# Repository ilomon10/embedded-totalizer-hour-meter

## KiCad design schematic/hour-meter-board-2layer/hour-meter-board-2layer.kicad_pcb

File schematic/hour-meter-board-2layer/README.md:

# Hour Meter main board, 2-layer variant (rev B)

This is the [rev-B main board](../hour-meter-board/README.md) routed on **2 copper layers** instead of 4, for a cheaper PCB. The circuit, parts, BOM and placement are the same; only the copper layers and the routing differ. It takes the same plug-on [PSU-B](../hour-meter-psu-b/README.md).

The folder is a copy of `../hour-meter-board`, made the way KiCad's *File → Save As* makes one, so the 4-layer design is unchanged. The build, routing and finishing scripts are the main board's: `tools-pcb.py` here runs them on this folder's files with 2 layers.

| | |
|---|---|
| Schematic | `hour-meter-board-2layer.kicad_sch` + the 8 module sheets: a copy of the main board's, with the same netlist. For the circuit, connectors, jumpers and pin map, see the [main board README](../hour-meter-board/README.md) |
| PCB | `hour-meter-board-2layer.kicad_pcb`: 100 × 90 mm, 2 layers. F.Cu and B.Cu both carry tracks and a GND pour |
| Script | `tools-pcb.py` with `check`, `place`, `route [tries]`, `finish [passes]` or `production` |
| Order files | `production/`: Gerber zip, `BOM-hour-meter-board-2layer.csv`, `CPL-hour-meter-board-2layer.csv` (JLCPCB columns). The BOM and CPL are byte-identical to the 4-layer board's, so assembly is the same; only the bare PCB differs |

**Checks at this revision (2026-10-21):**
- **ERC:** same schematic as the main board: 0 errors, 2 intended warnings.
- **DRC:** 0 errors, 0 unconnected items, 0 schematic-parity issues. The 22 warnings are the same silkscreen ones as on the 4-layer board.
- **Routing:** with the IMU keep-outs in place, Freerouting's first try connected everything, so `finish` had nothing left to do.
- **Stock:** all parts are in JLCPCB stock for 10 boards.

## What changes with 2 layers

| | 4 layers (`hour-meter-board`) | 2 layers (this board) |
|---|---|---|
| GND | Solid In1.Cu plane; GND pads drop to it through vias | Routed as tracks, plus a GND pour on F.Cu and on B.Cu |
| +3V3 | Pour on In2.Cu | Routed as tracks (Plane netclass, 0.3 mm) |
| Signal layers | F.Cu, In2.Cu, B.Cu | F.Cu, B.Cu |
| Under the IMU (U601, U602) | In1.Cu GND plane shields the chips from the tracks below | Keep-outs on both layers: no tracks or vias, GND pour only (see below) |
| Silkscreen | `HOUR METER rev B` | `HOUR METER rev B`, plus `2-LAYER` to its left |

Unchanged: the outline, placement, parts, netclasses, via sizes (0.5/0.25 mm; 0.8/0.4 mm on power and vehicle nets), the copper keep-out under the antenna, and no pour on the vehicle side.

**IMU keep-outs.** The MPU-6500 datasheet prohibits routing under the package. It also asks for no active signals on unshielded layers directly below the gyro, because its drive frequencies (24–30 kHz) can couple in. With only 2 layers nothing shields B.Cu, so `tools-pcb.py place` adds rule areas under U601 and U602 (the LIS3MDL magnetometer gets the same treatment):
- **F.Cu:** the space inside the pad ring.
- **B.Cu:** the package plus 0.5 mm.

They keep tracks and vias out, but let the GND pours in. Keep them if you re-route by hand; KiCad's DRC flags anything that enters them.

## Before you order

The main board's [Before you order](../hour-meter-board/README.md#before-you-order) list applies here too. In addition:

1. **GND return paths.** Without a plane, tracks cut the GND pours into pieces that are joined by vias and the other layer's pour. DRC confirms GND is fully connected, but the paths can be long.
   - **Main split:** on B.Cu, a bundle of tracks running down from the ESP32 module to the ports (x ≈ 170–178 mm) divides the pour.
   - **What to do:** look at both pours in KiCad and add stitching vias along that bundle and wherever a piece hangs on a narrow neck, mainly around the ESP32, the USB parts (J201, U203, U202) and the IMU.
2. **USB D+/D−.** On a 1.6 mm 2-layer board, a 90 Ω pair would need traces about 1 mm wide. Keep the pair short, side by side and over unbroken GND on the other layer instead; at 12 Mbit/s that is enough.
3. **AMS1117 heat.** U204's tab has no +3V3 plane to spread heat into. If the ESP32 transmits a lot, give the tab more +3V3 copper.
4. **JLCPCB order:** 2 layers, 1.6 mm.
   - **Smallest holes:** the 0.25 mm routed vias (0.5 mm pad) and the ESP32's 0.2 mm thermal-pad vias (0.6 mm pad).
   - **Via price:** JLCPCB's [capabilities page](https://jlcpcb.com/capabilities/pcb-capabilities) (checked 2026-10-21) allows 0.15 mm via holes on 2-layer boards. It charges extra for a 0.2–0.25 mm hole only when the via is under 0.45 mm across, so these vias should be standard price. Check the price after you choose the via option on the order form.

## Re-generating the board

```bash
python3 tools-pcb.py place        # placement: PLACEMENT in ../hour-meter-board/tools-build-pcb.py
python3 tools-pcb.py route 4      # Freerouting x4, keep the best -> GND pours
python3 tools-pcb.py finish 3     # close what Freerouting left open (exit 1 if anything is still open)
kicad-cli pcb drc --severity-all --schematic-parity hour-meter-board-2layer.kicad_pcb
python3 tools-pcb.py production   # production/: Gerber zip, BOM, CPL
```

## Compact variant

[`../hour-meter-board-compact`](../hour-meter-board-compact/README.md) is a copy of this board on 80 × 70 mm. It also has milled isolation slots and the fault fixes from [`../fault-analysis`](../fault-analysis/README.md): a fault-protected RS485 transceiver and fused 5 V header pins.

## Keeping the two boards in step

- **Schematic:** this one is a copy, so a circuit change has to go into both. To check they still match, export each netlist with `kicad-cli sch export netlist` and diff them.
- **Placement:** a change to `PLACEMENT` in `../hour-meter-board/tools-build-pcb.py` moves parts on both boards the next time each one is placed.

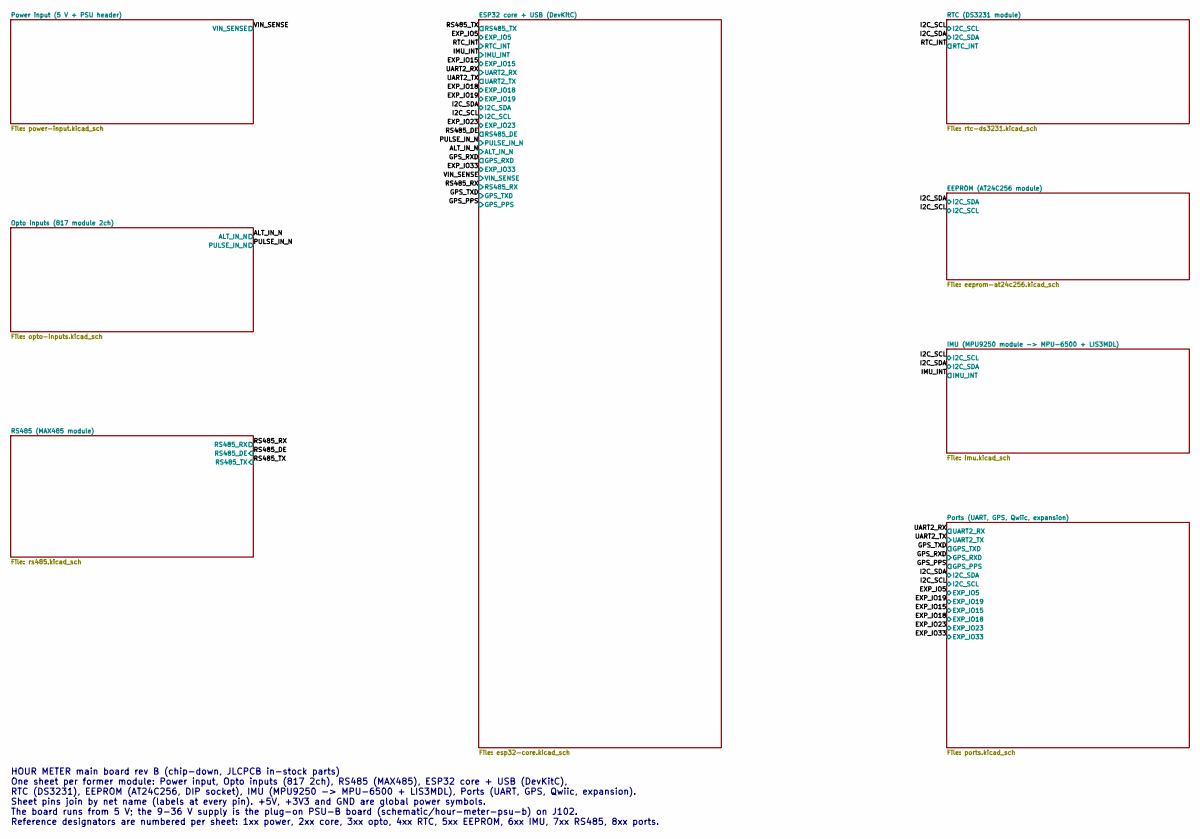
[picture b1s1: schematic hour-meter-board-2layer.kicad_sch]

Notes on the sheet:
HOUR METER main board rev B (chip-down, JLCPCB in-stock parts) One sheet per former module: Power input, Opto inputs (817 2ch), RS485 (MAX485), ESP32 core + USB (DevKitC), RTC (DS3231), EEPROM (AT24C256, DIP socket), IMU (MPU9250 -> MPU-6500 + LIS3MDL), Ports (UART, GPS, Qwiic, expansion). Sheet pi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

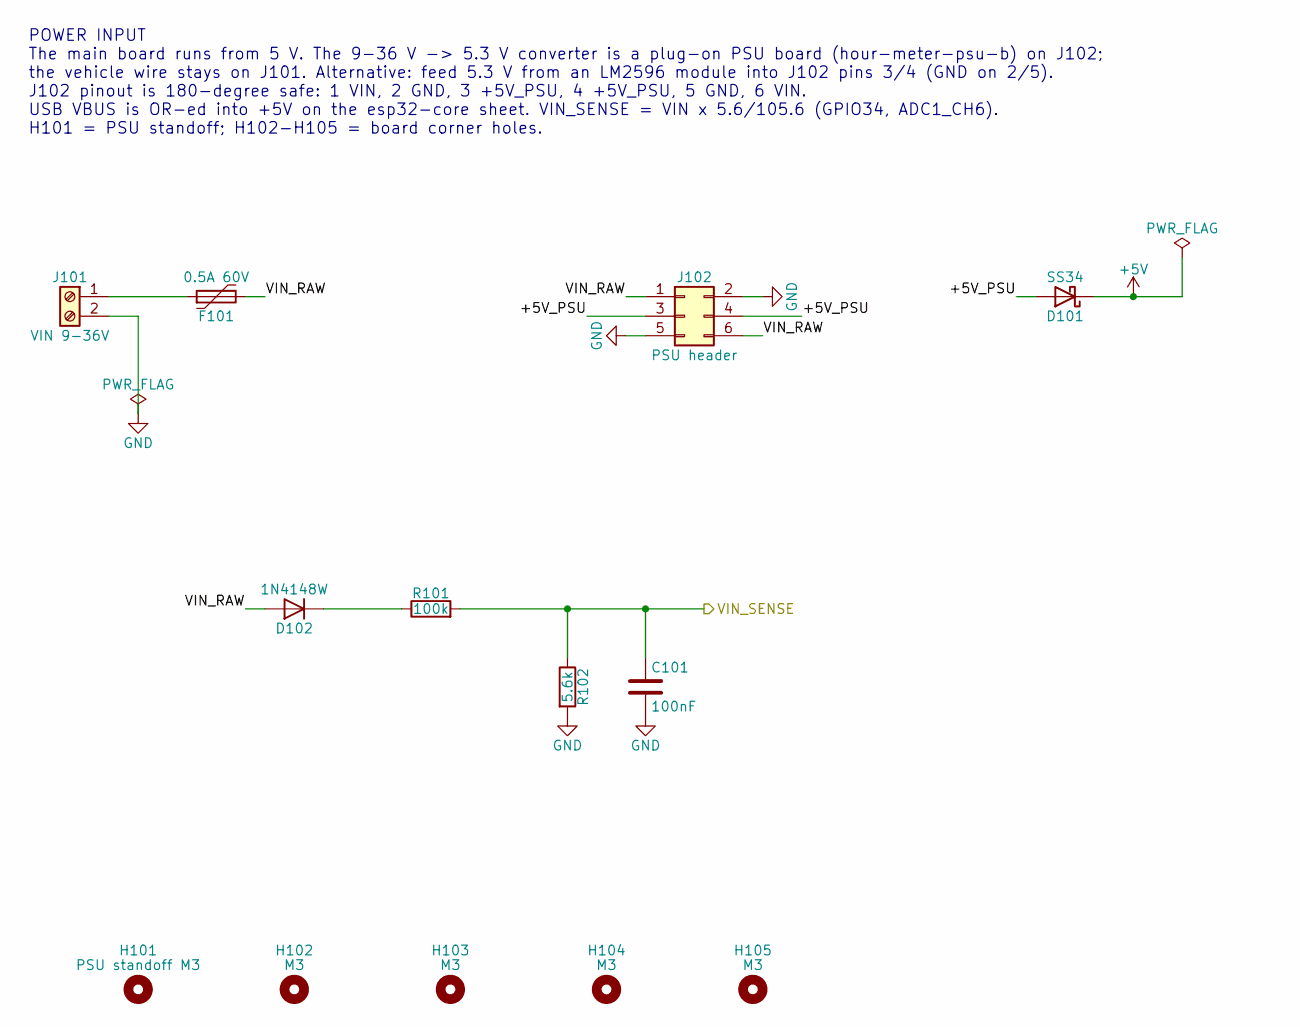
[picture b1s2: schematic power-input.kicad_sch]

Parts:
C101: 100nF; C_0603_1608Metric; MPN CC0603KRX7R9BB104; LCSC C14663
D101: SS34; D_SMA; MPN SS34; LCSC C8678
D102: 1N4148W; D_SOD-123; MPN 1N4148W; LCSC C81598
F101: 0.5A 60V; Fuse_1812_4532Metric; MPN 1812L050/60GR; LCSC C19078719
H101: PSU standoff M3; MountingHole_3.2mm_M3
H102, H103, H104, H105: M3; MountingHole_3.2mm_M3
J101: VIN 9-36V; TerminalBlock_Phoenix_MKDS-1,5-2-5.08_1x02_P5.08mm_Horizont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; MPN KF128-5.08-2P-AA; LCSC C474952
J102: PSU header; PinSocket_2x03_P2.54mm_Vertical; MPN A2541HWV-2x3P; LCSC C239343
R101: 100k; R_1206_3216Metric; MPN 1206W4F1003T5E; LCSC C17900
R102: 5.6k; R_0603_1608Metric; MPN 0603WAF5601T5E; LCSC C23189

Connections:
+5V: D101.1 (K); also elsewhere on the board
/Power input (5 V + PSU header)/+5V_PSU: D101.2 (A), J102.3, J102.4
/Power input (5 V + PSU header)/VIN_RAW: D102.2 (A), F101.2, J102.1, J102.6
/VIN_SENSE: C101.1, R101.2, R102.1; also elsewhere on the board
GND: C101.2, J101.2, J102.2, J102.5, R102.2; also elsewhere on the board
unnamed: D102.1 (K), R101.1
unnamed: F101.1, J101.1

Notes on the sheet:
POWER INPUT The main board runs from 5 V. The 9-36 V -> 5.3 V converter is a plug-on PSU board (hour-meter-psu-b) on J102; the vehicle wire stays on J101. Alternative: feed 5.3 V from an LM2596 module into J102 pins 3/4 (GND on 2/5). J102 pinout is 180-degree safe: 1 VIN, 2 GND, 3 +5V_PSU, 4 +5V_PS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

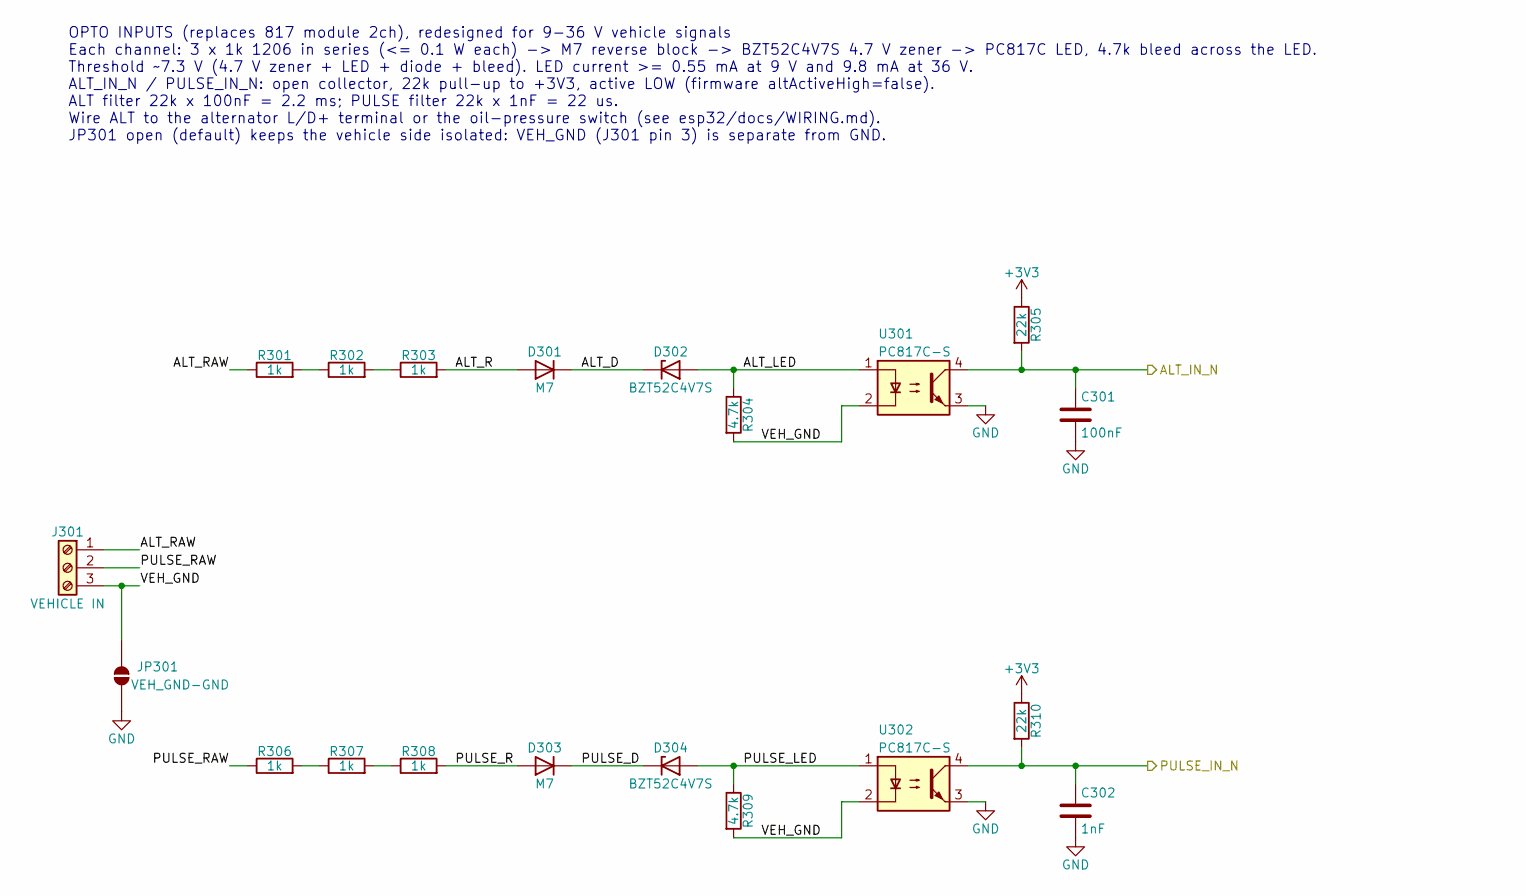
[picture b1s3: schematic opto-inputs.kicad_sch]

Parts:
C301: 100nF; C_0603_1608Metric; MPN CC0603KRX7R9BB104; LCSC C14663
C302: 1nF; C_0603_1608Metric; MPN CL10B102KB8NNNC; LCSC C1588
D301, D303: M7; D_SMA; MPN M7; LCSC C82443
D302, D304: BZT52C4V7S; D_SOD-323; MPN BZT52C4V7S; LCSC C22611
J301: VEHICLE IN; TerminalBlock_Phoenix_MKDS-1,5-3-5.08_1x03_P5.08mm_Horizont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; MPN KF128-5.08-3P-AA; LCSC C474953
JP301: VEH_GND-GND; SolderJumper-2_P1.3mm_Open_RoundedPad1.0x1.5mm
R301, R302, R303, R306, R307, R308: 1k; R_1206_3216Metric; MPN 1206W4F1001T5E; LCSC C4410
R304, R309: 4.7k; R_0603_1608Metric; MPN 0603WAF4701T5E; LCSC C23162
R305, R310: 22k; R_0603_1608Metric; MPN 0603WAF2202T5E; LCSC C31850
U301, U302: PC817C-S; SMDIP-4_W9.53mm; MPN PC817C-S; LCSC C3008369

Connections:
+3V3: R305.1, R310.1; also elsewhere on the board
/ALT_IN_N: C301.1, R305.2, U301.4; also elsewhere on the board
/Opto inputs (817 module 2ch)/ALT_D: D301.1 (K), D302.1 (K)
/Opto inputs (817 module 2ch)/ALT_LED: D302.2 (A), R304.1, U301.1
/Opto inputs (817 module 2ch)/ALT_R: D301.2 (A), R303.2
/Opto inputs (817 module 2ch)/ALT_RAW: J301.1, R301.1
/Opto inputs (817 module 2ch)/PULSE_D: D303.1 (K), D304.1 (K)
/Opto inputs (817 module 2ch)/PULSE_LED: D304.2 (A), R309.1, U302.1
/Opto inputs (817 module 2ch)/PULSE_R: D303.2 (A), R308.2
/Opto inputs (817 module 2ch)/PULSE_RAW: J301.2, R306.1
/Opto inputs (817 module 2ch)/VEH_GND: J301.3, JP301.1 (A), R304.2, R309.2, U301.2, U302.2
/PULSE_IN_N: C302.1, R310.2, U302.4; also elsewhere on the board
GND: C301.2, C302.2, JP301.2 (B), U301.3, U302.3; also elsewhere on the board
unnamed: R301.2, R302.1
unnamed: R302.2, R303.1
unnamed: R306.2, R307.1
unnamed: R307.2, R308.1

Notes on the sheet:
OPTO INPUTS (replaces 817 module 2ch), redesigned for 9-36 V vehicle signals Each channel: 3 x 1k 1206 in series (<= 0.1 W each) -> M7 reverse block -> BZT52C4V7S 4.7 V zener -> PC817C LED, 4.7k bleed across the LED. Threshold ~7.3 V (4.7 V zener + LED + diode + bleed). LED current >= 0.55 mA at 9 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

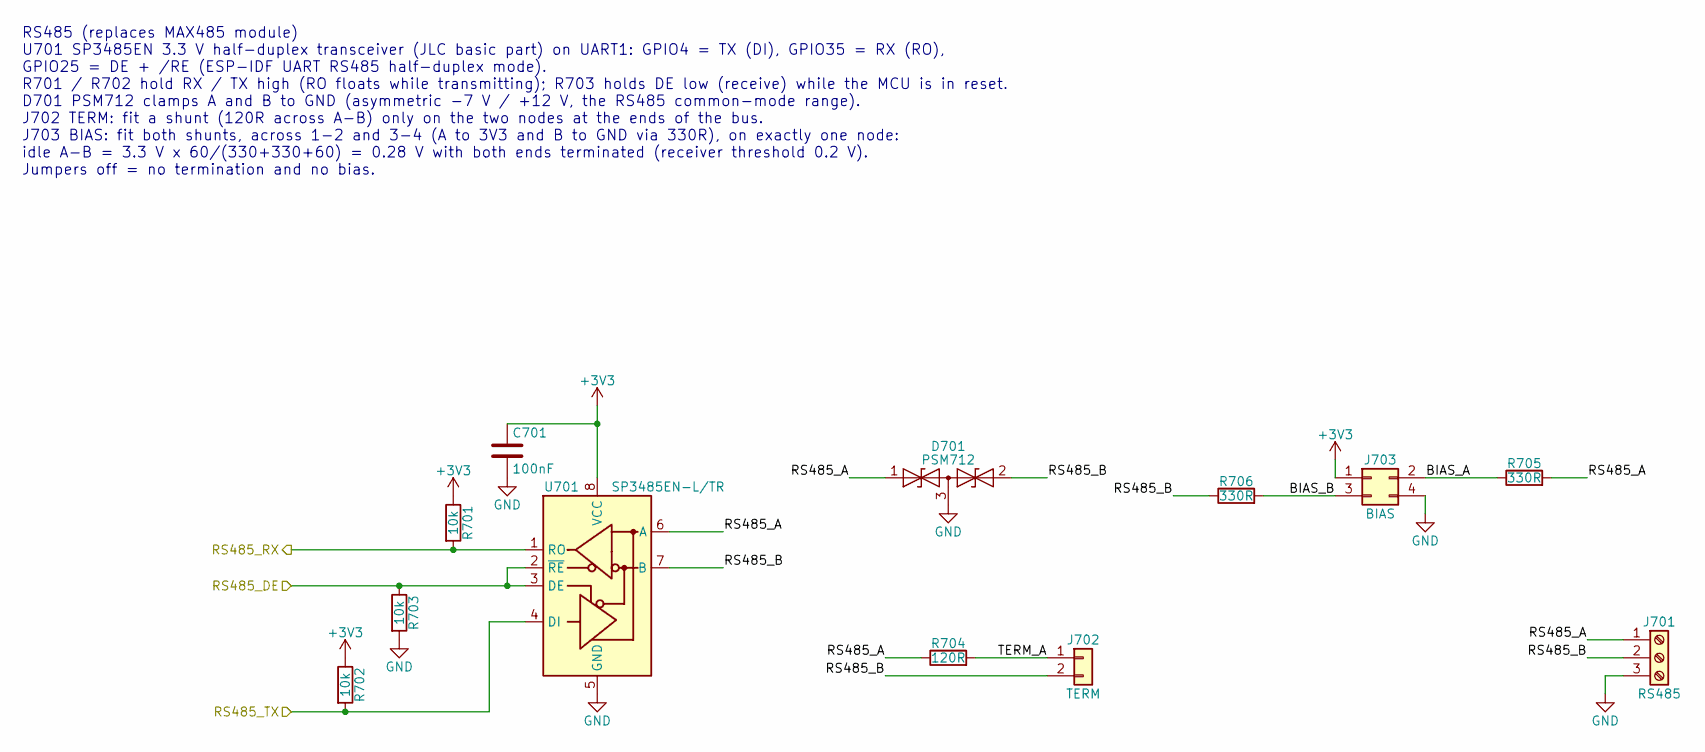
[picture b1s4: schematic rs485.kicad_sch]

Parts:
C701: 100nF; C_0603_1608Metric; MPN CC0603KRX7R9BB104; LCSC C14663
D701: PSM712; SOT-23; MPN PSM712-LF-T7; LCSC C32677
J701: RS485; TerminalBlock_Phoenix_MKDS-1,5-3-5.08_1x03_P5.08mm_Horizont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; MPN KF128-5.08-3P-AA; LCSC C474953
J702: TERM; PinHeader_1x02_P2.54mm_Vertical; MPN 254PZ-1x2P-V; LCSC C53055672
J703: BIAS; PinHeader_2x02_P2.54mm_Vertical; MPN 2.54-2*2PPin; LCSC C66690
R701, R702, R703: 10k; R_0603_1608Metric; MPN 0603WAF1002T5E; LCSC C25804
R704: 120R; R_0805_2012Metric; MPN 0805W8F1200T5E; LCSC C17437
R705, R706: 330R; R_0603_1608Metric; MPN 0603WAF3300T5E; LCSC C23138
U701: SP3485EN-L/TR; SOIC-8_3.9x4.9mm_P1.27mm; MPN SP3485EN-L/TR; LCSC C8963

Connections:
+3V3: C701.1, J703.1, R701.1, R702.1, U701.8 (VCC); also elsewhere on the board
/RS485 (MAX485 module)/BIAS_A: J703.2, R705.1
/RS485 (MAX485 module)/BIAS_B: J703.3, R706.2
/RS485 (MAX485 module)/RS485_A: D701.1 (A1), J701.1, R704.1, R705.2, U701.6 (A)
/RS485 (MAX485 module)/RS485_B: D701.2 (A2), J701.2, J702.2, R706.1, U701.7 (B)
/RS485 (MAX485 module)/TERM_A: J702.1, R704.2
/RS485_DE: R703.1, U701.2 (~RE), U701.3 (DE); also elsewhere on the board
/RS485_RX: R701.2, U701.1 (RO); also elsewhere on the board
/RS485_TX: R702.2, U701.4 (DI); also elsewhere on the board
GND: C701.2, D701.3 (common), J701.3, J703.4, R703.2, U701.5 (GND); also elsewhere on the board

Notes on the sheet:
RS485 (replaces MAX485 module) U701 SP3485EN 3.3 V half-duplex transceiver (JLC basic part) on UART1: GPIO4 = TX (DI), GPIO35 = RX (RO), GPIO25 = DE + /RE (ESP-IDF UART RS485 half-duplex mode). R701 / R702 hold RX / TX high (RO floats while transmitting); R703 holds DE low (receive) while the MCU i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

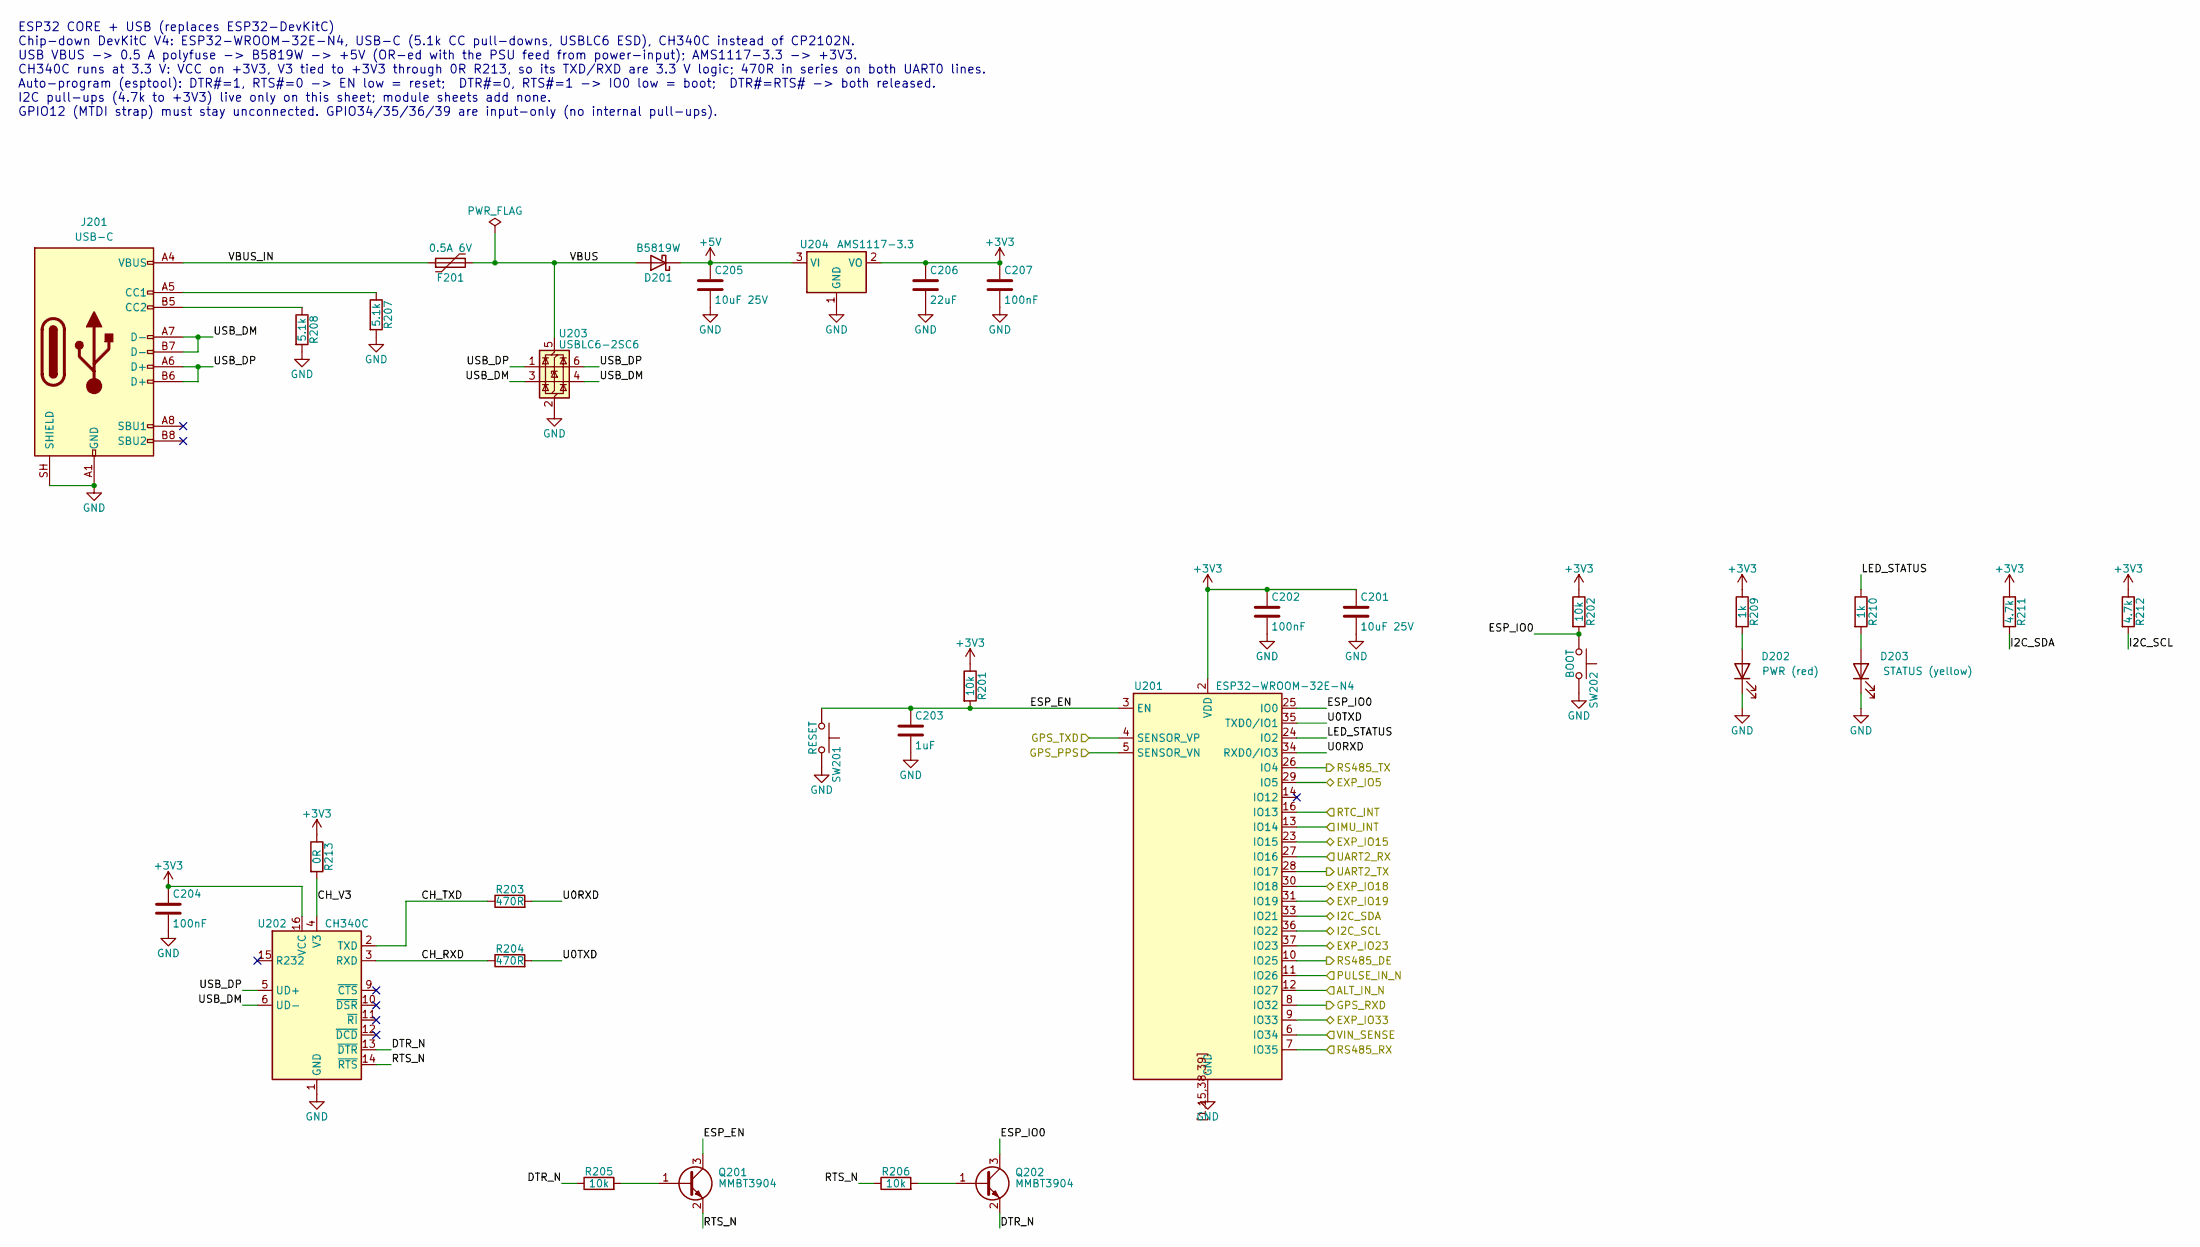
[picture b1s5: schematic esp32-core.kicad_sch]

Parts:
C201, C205: 10uF 25V; C_0805_2012Metric; MPN CL21A106KAYNNNE; LCSC C15850
C202, C204, C207: 100nF; C_0603_1608Metric; MPN CC0603KRX7R9BB104; LCSC C14663
C203: 1uF; C_0603_1608Metric; MPN CL10A105KB8NNNC; LCSC C15849
C206: 22uF; C_0805_2012Metric; MPN CL21A226MAQNNNE; LCSC C45783
D201: B5819W; D_SOD-123; MPN B5819W SL; LCSC C8598
D202: PWR (red); LED_0603_1608Metric; MPN KT-0603R; LCSC C2286
D203: STATUS (yellow); LED_0603_1608Metric; MPN KT-0603Y; LCSC C2287
F201: 0.5A 6V; Fuse_1206_3216Metric; MPN nSMD050; LCSC C69688
J201: USB-C; USB_C_Receptacle_HRO_TYPE-C-31-M-12; MPN TYPE-C-31-M-12; LCSC C165948
Q201, Q202: MMBT3904; SOT-23; MPN MMBT3904; LCSC C20526
R201, R202, R205, R206: 10k; R_0603_1608Metric; MPN 0603WAF1002T5E; LCSC C25804
R203, R204: 470R; R_0603_1608Metric; MPN 0603WAF4700T5E; LCSC C23179
R207, R208: 5.1k; R_0603_1608Metric; MPN 0603WAF5101T5E; LCSC C23186
R209, R210: 1k; R_0603_1608Metric; MPN 0603WAF1001T5E; LCSC C21190
R211, R212: 4.7k; R_0603_1608Metric; MPN 0603WAF4701T5E; LCSC C23162
R213: 0R; R_0603_1608Metric; MPN 0603WAF0000T5E; LCSC C21189
SW201: RESET; SW_Push_1P1T_XKB_TS-1187A; MPN TS-1187A-B-A-B; LCSC C318884
SW202: BOOT; SW_Push_1P1T_XKB_TS-1187A; MPN TS-1187A-B-A-B; LCSC C318884
U201: ESP32-WROOM-32E-N4; ESP32-WROOM-32E; MPN ESP32-WROOM-32E-N4; LCSC C701341
U202: CH340C; SOIC-16_3.9x9.9mm_P1.27mm; MPN CH340C; LCSC C84681
U203: USBLC6-2SC6; SOT-23-6; MPN USBLC6-2SC6; LCSC C7519
U204: AMS1117-3.3; SOT-223-3_TabPin2; MPN AMS1117-3.3; LCSC C6186

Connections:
+3V3: C201.1, C202.1, C204.1, C206.1, C207.1, R201.1, R202.1, R209.1, R211.1, R212.1, R213.1, U201.2 (VDD), U202.16 (VCC), U204.2 (VO); also elsewhere on the board
+5V: C205.1, D201.1 (K), U204.3 (VI); also elsewhere on the board
/ALT_IN_N: U201.12 (IO27); also elsewhere on the board
/ESP32 core + USB (DevKitC)/CH_RXD: R204.1, U202.3 (RXD)
/ESP32 core + USB (DevKitC)/CH_TXD: R203.1, U202.2 (TXD)
/ESP32 core + USB (DevKitC)/CH_V3: R213.2, U202.4 (V3)
/ESP32 core + USB (DevKitC)/DTR_N: Q202.2 (E), R205.1, U202.13 (~DTR)
/ESP32 core + USB (DevKitC)/ESP_EN: C203.1, Q201.3 (C), R201.2, SW201.1, U201.3 (EN)
/ESP32 core + USB (DevKitC)/ESP_IO0: Q202.3 (C), R202.2, SW202.1, U201.25 (IO0)
/ESP32 core + USB (DevKitC)/LED_STATUS: R210.1, U201.24 (IO2)
/ESP32 core + USB (DevKitC)/RTS_N: Q201.2 (E), R206.1, U202.14 (~RTS)
/ESP32 core + USB (DevKitC)/U0RXD: R203.2, U201.34 (RXD0/IO3)
/ESP32 core + USB (DevKitC)/U0TXD: R204.2, U201.35 (TXD0/IO1)
/ESP32 core + USB (DevKitC)/USB_DM: J201.A7 (D-), J201.B7 (D-), U202.6 (UD-), U203.3 (I/O2), U203.4 (I/O2)
/ESP32 core + USB (DevKitC)/USB_DP: J201.A6 (D+), J201.B6 (D+), U202.5 (UD+), U203.1 (I/O1), U203.6 (I/O1)
/ESP32 core + USB (DevKitC)/VBUS: D201.2 (A), F201.2, U203.5 (VBUS)
/ESP32 core + USB (DevKitC)/VBUS_IN: F201.1, J201.A4 (VBUS), J201.A9 (VBUS), J201.B4 (VBUS), J201.B9 (VBUS)
/EXP_IO5: U201.29 (IO5); also elsewhere on the board
/EXP_IO15: U201.23 (IO15); also elsewhere on the board
/EXP_IO18: U201.30 (IO18); also elsewhere on the board
/EXP_IO19: U201.31 (IO19); also elsewhere on the board
/EXP_IO23: U201.37 (IO23); also elsewhere on the board
/EXP_IO33: U201.9 (IO33); also elsewhere on the board
/GPS_PPS: U201.5 (SENSOR_VN); also elsewhere on the board
/GPS_RXD: U201.8 (IO32); also elsewhere on the board
/GPS_TXD: U201.4 (SENSOR_VP); also elsewhere on the board
/I2C_SCL: R212.2, U201.36 (IO22); also elsewhere on the board
/I2C_SDA: R211.2, U201.33 (IO21); also elsewhere on the board
/IMU_INT: U201.13 (IO14); also elsewhere on the board
/PULSE_IN_N: U201.11 (IO26); also elsewhere on the board
/RS485_DE: U201.10 (IO25); also elsewhere on the board
/RS485_RX: U201.7 (IO35); also elsewhere on the board
/RS485_TX: U201.26 (IO4); also elsewhere on the board
/RTC_INT: U201.16 (IO13); also elsewhere on the board
/UART2_RX: U201.27 (IO16); also elsewhere on the board
/UART2_TX: U201.28 (IO17); also elsewhere on the board
/VIN_SENSE: U201.6 (IO34); also elsewhere on the board
GND: C201.2, C202.2, C203.2, C204.2, C205.2, C206.2, C207.2, D202.1 (K), D203.1 (K), J201.A1 (GND), J201.A12 (GND), J201.B1 (GND), J201.B12 (GND), J201.SH (SHIELD), R207.2, R208.2, SW201.2, SW202.2, U201.1, U201.15, U201.38, U201.39, U201.[1,15,38,39] (GND), U202.1 (GND), U203.2 (GND), U204.1 (GND); also elsewhere on the board
unnamed: D202.2 (A), R209.2
unnamed: D203.2 (A), R210.2
unnamed: J201.A5 (CC1), R207.1
unnamed: J201.B5 (CC2), R208.1
unnamed: Q201.1 (B), R205.2
unnamed: Q202.1 (B), R206.2

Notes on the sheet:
ESP32 CORE + USB (replaces ESP32-DevKitC) Chip-down DevKitC V4: ESP32-WROOM-32E-N4, USB-C (5.1k CC pull-downs, USBLC6 ESD), CH340C instead of CP2102N. USB VBUS -> 0.5 A polyfuse -> B5819W -> +5V (OR-ed with the PSU feed from power-input); AMS1117-3.3 -> +3V3. CH340C runs at 3.3 V: VCC on +3V3, V3 t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

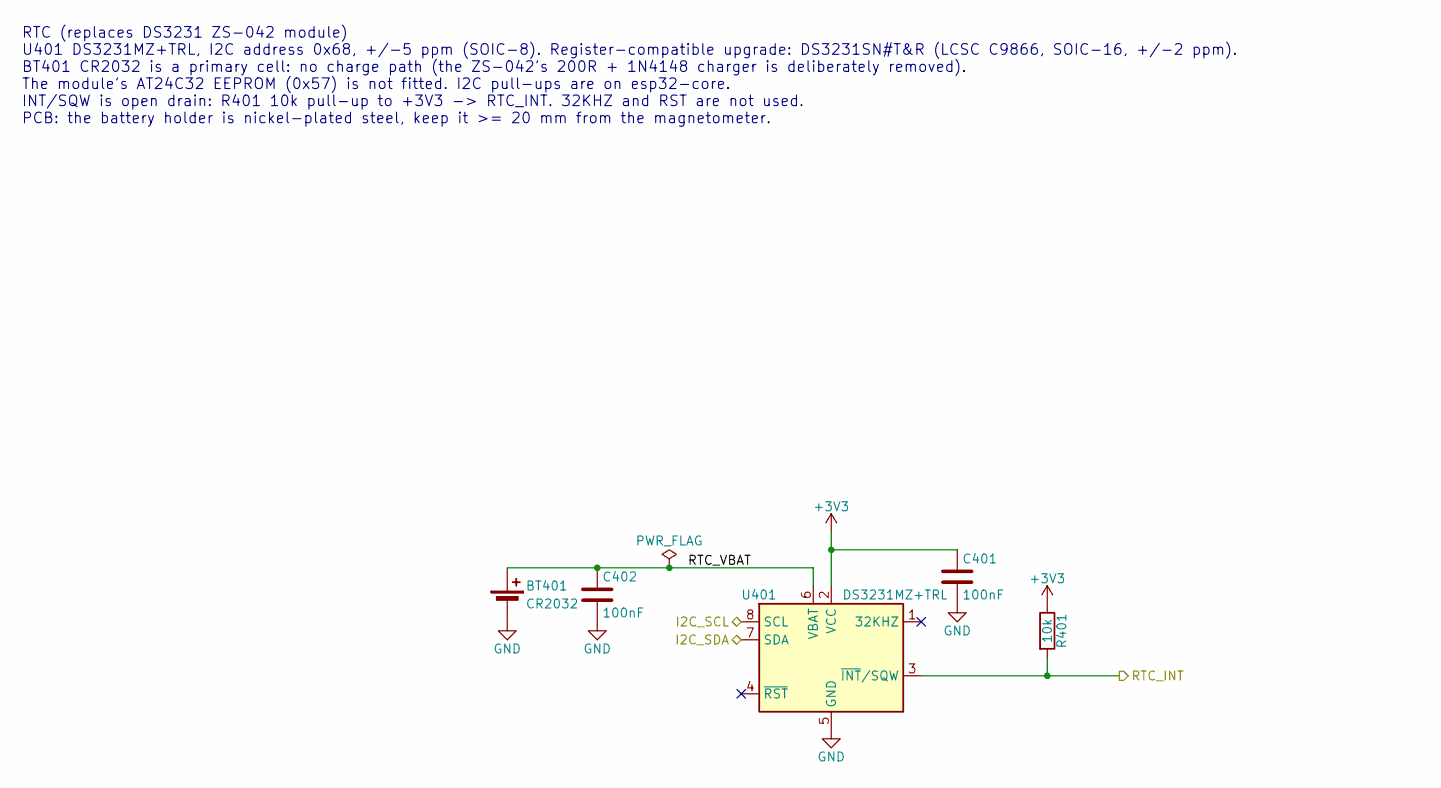
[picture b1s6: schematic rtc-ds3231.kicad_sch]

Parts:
BT401: CR2032; BatteryHolder_MYOUNG_BS-07-A1BJ001_CR2032; MPN BS-07-A1BJ001; LCSC C2979167
C401, C402: 100nF; C_0603_1608Metric; MPN CC0603KRX7R9BB104; LCSC C14663
R401: 10k; R_0603_1608Metric; MPN 0603WAF1002T5E; LCSC C25804
U401: DS3231MZ+TRL; SOIC-8_3.9x4.9mm_P1.27mm; MPN DS3231MZ+TRL; LCSC C107410

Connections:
+3V3: C401.1, R401.1, U401.2 (VCC); also elsewhere on the board
/I2C_SCL: U401.8 (SCL); also elsewhere on the board
/I2C_SDA: U401.7 (SDA); also elsewhere on the board
/RTC (DS3231 module)/RTC_VBAT: BT401.1 (+), C402.1, U401.6 (VBAT)
/RTC_INT: R401.2, U401.3 (~INT/SQW); also elsewhere on the board
GND: BT401.2 (-), C401.2, C402.2, U401.5 (GND); also elsewhere on the board

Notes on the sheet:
RTC (replaces DS3231 ZS-042 module) U401 DS3231MZ+TRL, I2C address 0x68, +/-5 ppm (SOIC-8). Register-compatible upgrade: DS3231SN#T&R (LCSC C9866, SOIC-16, +/-2 ppm). BT401 CR2032 is a primary cell: no charge path (the ZS-042's 200R + 1N4148 charger is deliberately removed). The module's AT24C32 EE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

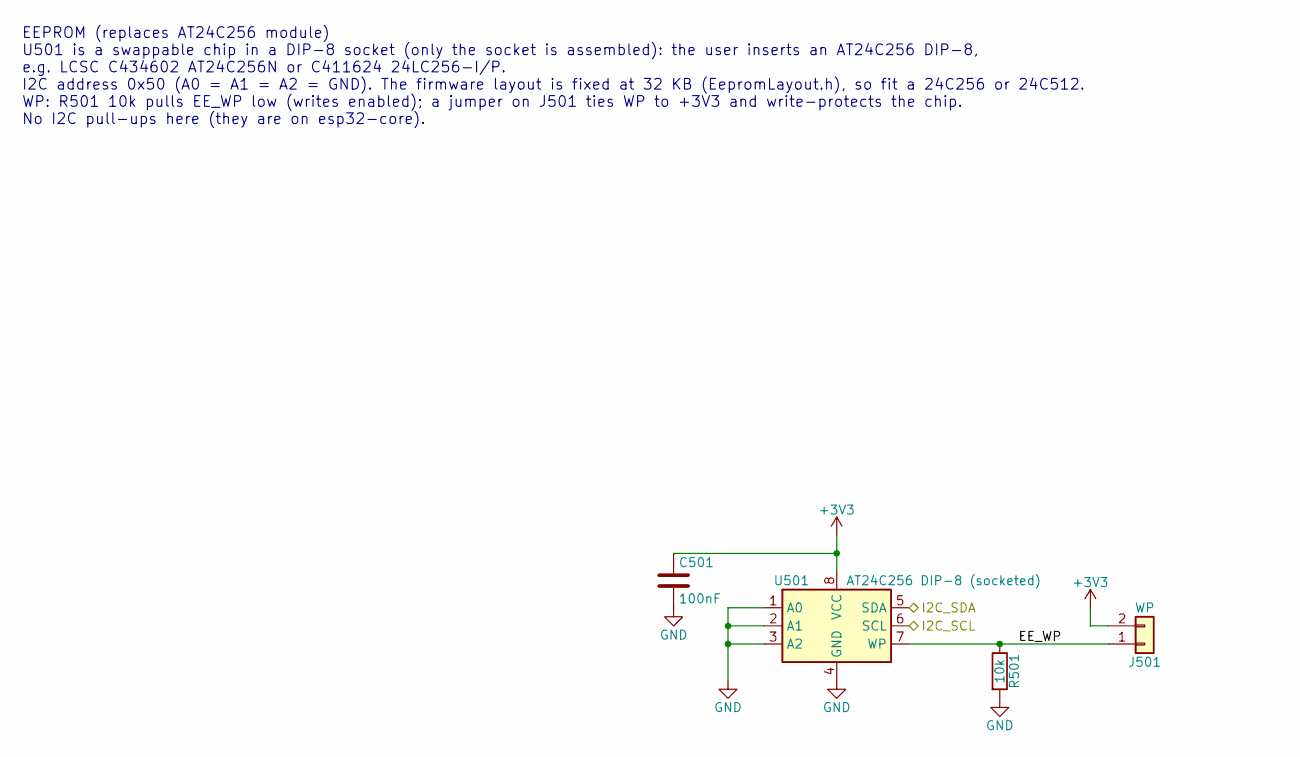
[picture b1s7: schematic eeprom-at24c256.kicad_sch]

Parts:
C501: 100nF; C_0603_1608Metric; MPN CC0603KRX7R9BB104; LCSC C14663
J501: WP; PinHeader_1x02_P2.54mm_Vertical; MPN 254PZ-1x2P-V; LCSC C53055672
R501: 10k; R_0603_1608Metric; MPN 0603WAF1002T5E; LCSC C25804
U501: AT24C256 DIP-8 (socketed); DIP-8_W7.62mm_Socket; MPN IC254V-12-08-0743; LCSC C2874007

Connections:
+3V3: C501.1, J501.2, U501.8 (VCC); also elsewhere on the board
/EEPROM (AT24C256 module)/EE_WP: J501.1, R501.1, U501.7 (WP)
/I2C_SCL: U501.6 (SCL); also elsewhere on the board
/I2C_SDA: U501.5 (SDA); also elsewhere on the board
GND: C501.2, R501.2, U501.1 (A0), U501.2 (A1), U501.3 (A2), U501.4 (GND); also elsewhere on the board

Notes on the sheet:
EEPROM (replaces AT24C256 module) U501 is a swappable chip in a DIP-8 socket (only the socket is assembled): the user inserts an AT24C256 DIP-8, e.g. LCSC C434602 AT24C256N or C411624 24LC256-I/P. I2C address 0x50 (A0 = A1 = A2 = GND). The firmware layout is fixed at 32 KB (EepromLayout.h), so fit 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

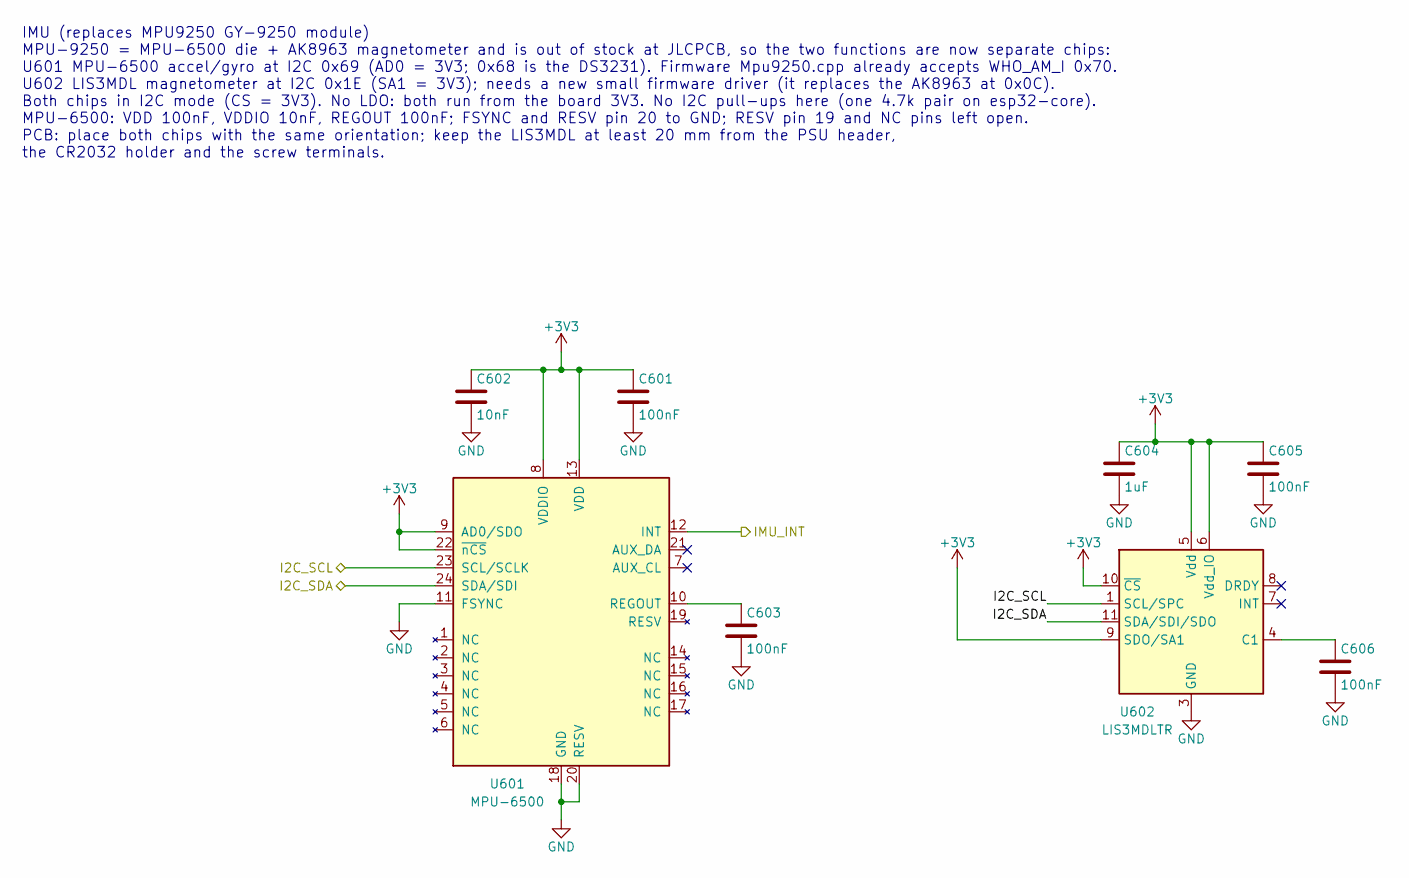
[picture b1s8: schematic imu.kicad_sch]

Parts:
C601, C603, C605, C606: 100nF; C_0603_1608Metric; MPN CC0603KRX7R9BB104; LCSC C14663
C602: 10nF; C_0603_1608Metric; MPN 0603B103K500NT; LCSC C57112
C604: 1uF; C_0603_1608Metric; MPN CL10A105KB8NNNC; LCSC C15849
U601: MPU-6500; InvenSense_QFN-24_3x3mm_P0.4mm; MPN MPU-6500; LCSC C50278
U602: LIS3MDLTR; LGA-12_2x2mm_P0.5mm; MPN LIS3MDLTR; LCSC C478483

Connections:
+3V3: C601.1, C602.1, C604.1, C605.1, U601.8 (VDDIO), U601.9 (AD0/SDO), U601.13 (VDD), U601.22 (~nCS), U602.5 (Vdd), U602.6 (Vdd_IO), U602.9 (SDO/SA1), U602.10 (~CS); also elsewhere on the board
/I2C_SCL: U601.23 (SCL/SCLK), U602.1 (SCL/SPC); also elsewhere on the board
/I2C_SDA: U601.24 (SDA/SDI), U602.11 (SDA/SDI/SDO); also elsewhere on the board
/IMU_INT: U601.12 (INT); also elsewhere on the board
GND: C601.2, C602.2, C603.2, C604.2, C605.2, C606.2, U601.11 (FSYNC), U601.18 (GND), U601.20 (RESV), U602.2 (GND), U602.3 (GND), U602.12 (GND); also elsewhere on the board
unnamed: C603.1, U601.10 (REGOUT)
unnamed: C606.1, U602.4 (C1)

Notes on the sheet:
IMU (replaces MPU9250 GY-9250 module) MPU-9250 = MPU-6500 die + AK8963 magnetometer and is out of stock at JLCPCB, so the two functions are now separate chips: U601 MPU-6500 accel/gyro at I2C 0x69 (AD0 = 3V3; 0x68 is the DS3231). Firmware Mpu9250.cpp already accepts WHO_AM_I 0x70. U602 LIS3MDL magn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

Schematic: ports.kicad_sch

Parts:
C801: 100nF; C_0603_1608Metric; MPN CC0603KRX7R9BB104; LCSC C14663
F801: 0.2A; Fuse_1206_3216Metric; MPN SMD1206P020TF; LCSC C20984
J801: UART; JST_XH_B4B-XH-A_1x04_P2.50mm_Vertical; MPN B4B-XH-A(LF)(SN); LCSC C144395
J802: GPS; PinSocket_1x05_P2.54mm_Vertical; MPN 2.54-1*5PFemale; LCSC C50950
J803: QWIIC; JST_SH_SM04B-SRSS-TB_1x04-1MP_P1.00mm_Horizontal; MPN SM04B-SRSS-TB(LF)(SN); LCSC C160404
J804: EXP; PinHeader_2x05_P2.54mm_Vertical; MPN A2541WV-2x5P; LCSC C225520
JP801: GPS VCC 3V3/5V; SolderJumper-3_P1.3mm_Bridged12_RoundedPad1.0x1.5mm
R801, R803, R804, R805: 100R; R_0603_1608Metric; MPN 0603WAF1000T5E; LCSC C22775
R802, R806, R807: 100k; R_0603_1608Metric; MPN 0603WAF1003T5E; LCSC C25803
U801: 74LVC1G17GW; SOT-353_SC-70-5; MPN 74LVC1G17GW,125; LCSC C426705
U802: SRV05-4; SOT-23-6; MPN SRV05-4-P-T7; LCSC C85364

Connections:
+3V3: C801.1, J803.2, J804.1, JP801.1 (A), R802.1, R806.1, U801.5 (VCC); also elsewhere on the board
+5V: F801.1, J804.2, JP801.3 (B), U802.5 (VP); also elsewhere on the board
/EXP_IO5: J804.3; also elsewhere on the board
/EXP_IO15: J804.7; also elsewhere on the board
/EXP_IO18: J804.4; also elsewhere on the board
/EXP_IO19: J804.5; also elsewhere on the board
/EXP_IO23: J804.6; also elsewhere on the board
/EXP_IO33: J804.8; also elsewhere on the board
/GPS_PPS: R805.2, R807.1; also elsewhere on the board
/GPS_RXD: R804.2; also elsewhere on the board
/GPS_TXD: R803.2, R806.2; also elsewhere on the board
/I2C_SCL: J803.4; also elsewhere on the board
/I2C_SDA: J803.3; also elsewhere on the board
/Ports (UART, GPS, Qwiic, expansion)/GPS_PPS_EXT: J802.5, R805.1
/Ports (UART, GPS, Qwiic, expansion)/GPS_RX_EXT: J802.4, R804.1, U802.6 (IO4)
/Ports (UART, GPS, Qwiic, expansion)/GPS_TX_EXT: J802.3, R803.1, U802.4 (IO3)
/Ports (UART, GPS, Qwiic, expansion)/GPS_VCC: J802.1, JP801.2 (C)
/Ports (UART, GPS, Qwiic, expansion)/UART_5V: F801.2, J801.1
/Ports (UART, GPS, Qwiic, expansion)/UART_RXD_EXT: J801.3, R802.2, U801.2, U802.3 (IO2)
/Ports (UART, GPS, Qwiic, expansion)/UART_TXD_EXT: J801.2, R801.1, U802.1 (IO1)
/UART2_RX: U801.4; also elsewhere on the board
/UART2_TX: R801.2; also elsewhere on the board
GND: C801.2, J801.4, J802.2, J803.1, J803.MP (MountPin), J804.9, J804.10, R807.2, U801.3 (GND), U802.2 (VN); also elsewhere on the board

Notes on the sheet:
PORTS J801 UART sensor port: UART2 = GPIO17 TX (3.3 V out via R801 100R) / GPIO16 RX via U801 74LVC1G17 (5 V-tolerant input, R802 keeps it idle-high); pin 1 = 5 V, 200 mA via F801 polyfuse. U802 SRV05-4 = ESD on the four external UART/GPS lines. J802 GPS card header for u-blox type modules: UART on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
